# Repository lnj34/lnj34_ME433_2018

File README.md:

# lnj34_ME433_2018
Hello World! This is my first commit
Another line

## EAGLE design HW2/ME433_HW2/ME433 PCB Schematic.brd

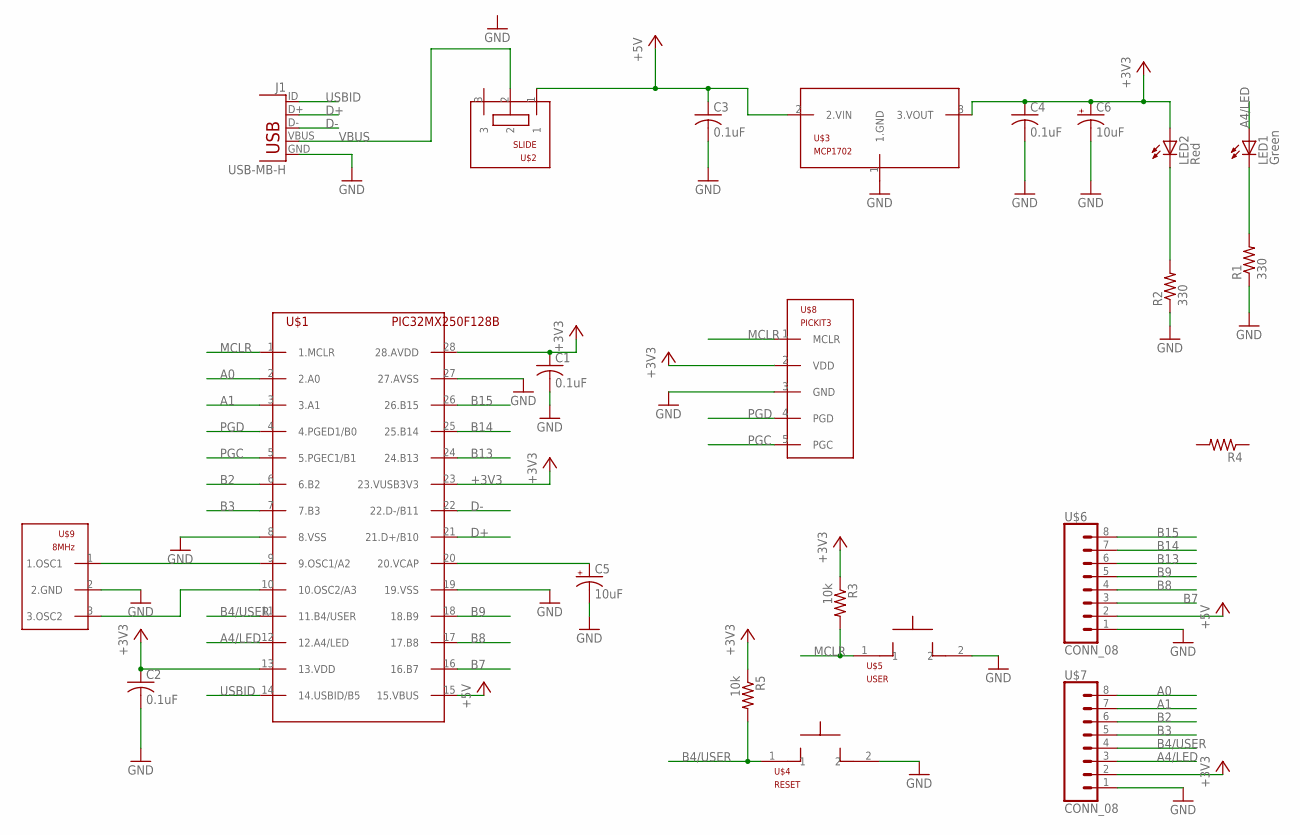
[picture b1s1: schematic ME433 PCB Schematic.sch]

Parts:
C1, C2, C3, C4: 0.1uF; C025-025X050
C5, C6: 10uF; B45181B
J1: USB-MB-H
LED1: Green; LED3MM
LED2: Red; LED3MM
R1, R2: 330; 0207/10
R3, R5: 10k; 0207/10
R4: R-US_0207/10; 0207/10
U$1: PIC32MX250F128B; DIL28-3
U$2: SLIDE
U$3: MCP1702; TO92
U$4: RESET; PB
U$5: USER; PB
U$6, U$7: CONN_08; 1X08
U$8: PICKIT3; 1X05
U$9: 8MHz; OSC

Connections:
+3V3: C1.1, C2.1, C4.1, C6.+, LED2.A, R3.1, R5.1, U$1.13 (13.VDD), U$1.23 (23.VUSB3V3), U$1.28 (28.AVDD), U$3.3 (3.VOUT), U$7.2, U$8.2 (VDD)
+5V: C3.1, U$1.15 (15.VBUS), U$2.1, U$3.2 (2.VIN), U$6.2
A0: U$1.2 (2.A0), U$7.8
A1: U$1.3 (3.A1), U$7.7
A4/LED: LED1.A, U$1.12 (12.A4/LED), U$7.3
B2: U$1.6 (6.B2), U$7.6
B3: U$1.7 (7.B3), U$7.5
B4/USER: R5.2, U$1.11 (11.B4/USER), U$4.1, U$7.4
B7: U$1.16 (16.B7), U$6.3
B8: U$1.17 (17.B8), U$6.4
B9: U$1.18 (18.B9), U$6.5
B13: U$1.24 (24.B13), U$6.6
B14: U$1.25 (25.B14), U$6.7
B15: U$1.26 (26.B15), U$6.8
D+: J1.D+, U$1.21 (21.D+/B10)
D-: J1.D-, U$1.22 (22.D-/B11)
GND: C1.2, C2.2, C3.2, C4.2, C5.-, C6.-, J1.GND, R1.1, R2.1, U$1.8 (8.VSS), U$1.19 (19.VSS), U$1.27 (27.AVSS), U$3.1 (1.GND), U$4.2, U$5.2, U$6.1, U$7.1, U$8.3 (GND), U$9.2 (2.GND)
MCLR: R3.2, U$1.1 (1.MCLR), U$5.1, U$8.1 (MCLR)
unnamed: LED1.K (C), R1.2
unnamed: LED2.K (C), R2.2
unnamed: U$1.9 (9.OSC1/A2), U$9.1 (1.OSC1)
unnamed: U$1.10 (10.OSC2/A3), U$9.3 (3.OSC2)
unnamed: C5.+, U$1.20 (20.VCAP)
PGC: U$1.5 (5.PGEC1/B1), U$8.5 (PGC)
PGD: U$1.4 (4.PGED1/B0), U$8.4 (PGD)
USBID: J1.ID, U$1.14 (14.USBID/B5)
VBUS: J1.VBUS, U$2.2

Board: 2 copper layers, 23 parts (0 on the bottom side), 27 nets, no tracks yet.

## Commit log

2018-04-08 Added another line
    Another line
2018-04-08 Main.c file created
2018-04-08 Nick's template
2018-04-08 Changed several parameters
2018-04-08 Finished parameters
2018-04-08 Fixed PWP
2018-04-08 Debugging
2018-04-09 Configuration complete
2018-04-09 editing TRIS and LATS
2018-04-09 Edits
2018-04-09 Turn LED on
2018-04-09 LED turns on
2018-04-10 Working Code!
2018-04-10 Make HW1 Folder
2018-04-10 Put README in main repo
2018-04-10 Relevant pictures for HW1
2018-04-10 Edited file name
2018-04-11 LED Cap effects
2018-04-13 .sch .lbr and .brd files completed
    used the wrong folder, not in my github folder accidentally, so all completed at once
2018-04-17 Finished PCB schematic, board and layout (in another folder first)
2018-04-21 Further edits
2018-04-21 Comments
2018-04-25 Fixed misplaced files
2018-04-26 Edits hw4
2018-04-30 Several more edits
2018-04-30 Screenshot of sine wave
    Could not think of a correct code to produce ramp wave, but tried my best.
2018-05-01 Circuit diagram
2018-05-01 HW5 work
2018-05-01 Edits and improvements
2018-05-01 Added HW5 back
2018-05-02 HW 6 edits
2018-05-19 finished Hw6
2018-05-19 Working on next Hw
2018-05-20 HW8 complete
2018-05-20 Create hw9
2018-05-23 Fixed various HWs
2018-05-23 Hw9 edits
2018-05-24 HW10
2018-05-26 HW 10 done
2018-05-27 HW11
2018-05-28 HW12 created and completed
2018-05-28 HW13 create and start work
2018-05-28 HW 13 before major edits
2018-05-28 HW13 fixed
2018-05-29 HW14 edits
2018-05-29 HW14 MPLAB code done
2018-05-29 HW14 android updates
2018-05-29 HW 14 edits from android USB git
2018-05-29 Edit folder names
2018-06-06 HW 15 images upload
2018-06-09 Reproduced HW 14 in HW 16
2018-06-09 HW 16 done
2018-06-11 HW 16 edits
2018-06-11 HW 16 updates
2018-06-11 HW 16 motor speed done
2018-06-12 Car android app
2018-06-12 HW14
2018-06-12 Revert "Car android app"
    This reverts commit 5362481f5b8a08b1c7c548b7daaf5f4220ac9a14.
2018-06-12 HW14 modified
2018-06-12 HW 14 update
2018-06-12 New commits broke App
2018-06-12 Made updates to HW14
    Do not Pull! It ruins everything!
2018-06-12 HW 17 edits
2018-06-12 HW 14 works
    build hw 18 on hw14
2018-06-12 HW 18
    Very big, has all of android usb code w/o removing anything yet
2018-06-12 New Hw18 to test
2018-06-13 HW18
    camera and android usb both work simultaneously
2018-06-13 HW 18 edits
2018-06-14 HW18 works!!!
2018-06-14 HW 18 works again
2018-06-14 Copied files to HW18 folder
